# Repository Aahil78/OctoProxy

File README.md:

# OctoProxy

OctoProxy is a raspberry pi based OctoPrint server for the Bambu Lab A1, it acts as a proxy for region locked and LAN Only mode printers to have remote monitoring and access. It also has a Tailscale VPN server to trick Bambu Studio to think you are on  your LAN when you arent, this will allow you to send prints from Bambu Studio to any LAN Only printer from anywhere in the world. You can also use it as a printago fuse or simplyprint server.

Features:
  - Runs OctoPrint allowing you to send prints from anywhere.
  - Uses a Raspberry Pi 4 as the SBC, allowing for upgrades like sensors, lights, software upgrades, and more.
  - WS2812B/SK6812 3 Pin connector for custom lights.
  - Has a CSI Camera, allowing better timelapses and better video streaming footage. We all know the A1 Camera is..... special.
  - GPIO Pins broken out for upgrades.

## Images

### PCB:

### Case:

(Top has magnets embedded)

### Schematic:

## BOM:

| Item:                            | Quantity: | Price: | Link:                | Total Cost:                   |
|----------------------------------|-----------|--------|----------------------|-------------------------------|
| Raspberry Pi 4 (Already have it) | 1         | $0     | N/A                  |                               |
| Raspberry Pi 4 Camera            | 1         | $23.08 | Camera               |                               |
| PCB                              | 1         | $15.78 |                      |                               |
| Raspberry Pi Fan                 | 1         | $4.35  | Fan                  |                               |
| Standoffs & Screws               | 1 kit     | $10    | Screws and standoffs |                               |
| 3 Pin Female Header              | 3         | $2.50  | 3 Pin Header         |                               |
| 4 Pin Female Header              | 2         | $2.72  | 4 Pin Header         |                               |
| 7 Pin Female Header              | 1         | $3.10  | 7 Pin Header         |                               |
| 6 Pin Female Header              | 2         | $2.95  | 6 Pin Header         |                               |
| 2 Pin Male Header                | 1         | $1.00  | 2 Pin Header         |                               |
| 1 Pin Header                     | 1         | $1     | 1 Pin Header         |                               |
| 330ohm Resistor                  | 1         | $1.47  | Resistor             |                               |
| 40Pin SMT Connector              | 1         | $4.77  | SMT Connector        |                               |
| WS2812B LED Strip                | 1         | $6.46  | LED Strip            |                               |
|                                  |           |        |                      | 79.18 (Will pay extra myself) |

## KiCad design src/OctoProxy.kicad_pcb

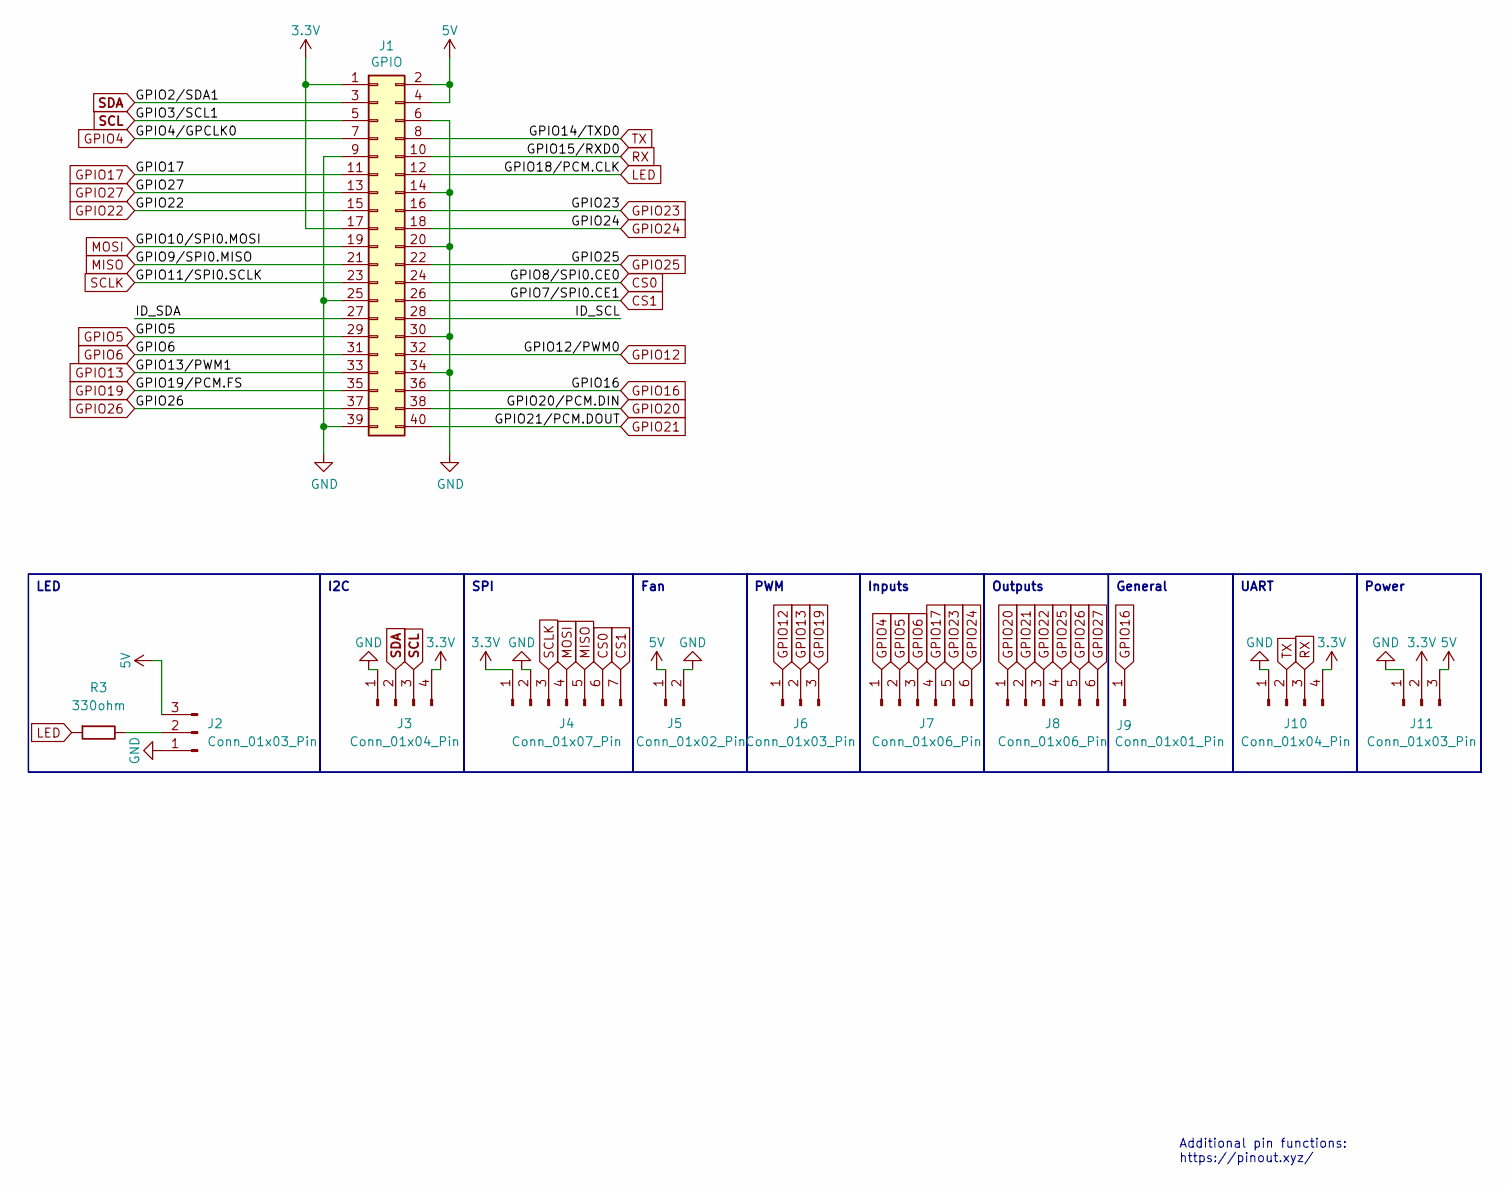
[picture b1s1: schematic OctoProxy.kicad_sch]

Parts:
J1: GPIO; Raspberry_Pi_Shield_Bottom_Entry_No_Mounting_Holes
J2, J6, J11: Conn_01x03_Pin; Harwin_M20-89003xx_1x03_P2.54mm_Horizontal
J3, J10: Conn_01x04_Pin; Harwin_M20-89004xx_1x04_P2.54mm_Horizontal
J4: Conn_01x07_Pin; Harwin_M20-89007xx_1x07_P2.54mm_Horizontal
J5: Conn_01x02_Pin; PinHeader_1x02_P2.54mm_Horizontal
J7, J8: Conn_01x06_Pin; Harwin_M20-89006xx_1x06_P2.54mm_Horizontal
J9: Conn_01x01_Pin; PinHeader_1x01_P2.54mm_Horizontal
R3: 330ohm; R_Axial_DIN0207_L6.3mm_D2.5mm_P10.16mm_Horizontal

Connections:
3.3V: J1.1, J1.17, J3.4, J4.1, J10.4, J11.2
5V: J1.2, J1.4, J2.3, J5.1, J11.3
/ID_SCL: J1.28
/ID_SDA: J1.27
CS0: J1.24, J4.6
CS1: J1.26, J4.7
GND: J1.6, J1.9, J1.14, J1.20, J1.25, J1.30, J1.34, J1.39, J2.1, J3.1, J4.2, J5.2, J10.1, J11.1
GPIO4: J1.7, J7.1
GPIO5: J1.29, J7.2
GPIO6: J1.31, J7.3
GPIO12: J1.32, J6.1
GPIO13: J1.33, J6.2
GPIO16: J1.36, J9.1
GPIO17: J1.11, J7.4
GPIO19: J1.35, J6.3
GPIO20: J1.38, J8.1
GPIO21: J1.40, J8.2
GPIO22: J1.15, J8.3
GPIO23: J1.16, J7.5
GPIO24: J1.18, J7.6
GPIO25: J1.22, J8.4
GPIO26: J1.37, J8.5
GPIO27: J1.13, J8.6
LED: J1.12, R3.1
MISO: J1.21, J4.5
MOSI: J1.19, J4.4
unnamed: J2.2, R3.2
RX: J1.10, J10.3
SCL: J1.5, J3.3
SCLK: J1.23, J4.3
SDA: J1.3, J3.2
TX: J1.8, J10.2

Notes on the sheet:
Additional pin functions: https://pinout.xyz/
Outputs
UART
LED
Power
I2C
SPI
PWM
Inputs
Fan
General

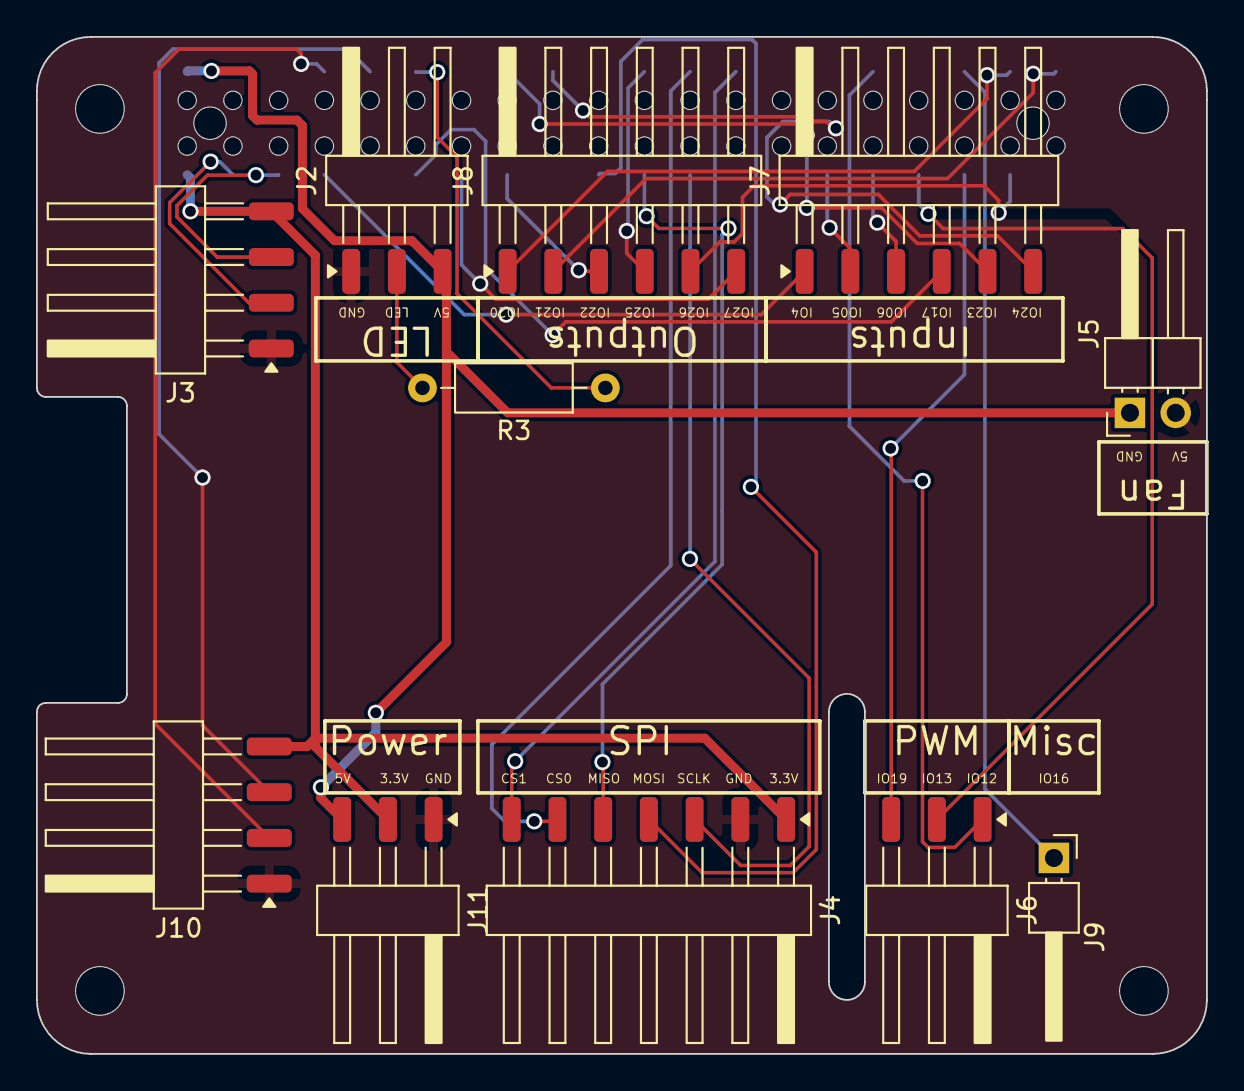
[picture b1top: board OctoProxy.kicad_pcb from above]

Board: 2 copper layers, 65.0 x 56.5 mm, 16 parts (0 on the bottom side), 30 nets.

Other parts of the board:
MH1, MH2, MH3, MH4: MountingHole_2.7mm_M2.5

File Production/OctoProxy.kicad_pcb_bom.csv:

Designator,Quantity,Value,Footprint,Package,MPN,DNP,Mount_Type,Description
J1,1,GPIO,Raspberry_Pi_Shield_Bottom_Entry_No_Mounting_Holes,,,,tht,
"J10, J3",2,Conn_01x04_Pin,Harwin_M20-89004xx_1x04_P2.54mm_Horizontal,,,,smt,
"J11, J2, J6",3,Conn_01x03_Pin,Harwin_M20-89003xx_1x03_P2.54mm_Horizontal,,,,smt,
J4,1,Conn_01x07_Pin,Harwin_M20-89007xx_1x07_P2.54mm_Horizontal,,,,smt,
J5,1,Conn_01x02_Pin,PinHeader_1x02_P2.54mm_Horizontal,,,,tht,"Generic connector, single row, 01x02, script generated"
"J7, J8",2,Conn_01x06_Pin,Harwin_M20-89006xx_1x06_P2.54mm_Horizontal,,,,smt,
J9,1,Conn_01x01_Pin,PinHeader_1x01_P2.54mm_Horizontal,,,,tht,"Generic connector, single row, 01x01, script generated"
R3,1,330ohm,R_Axial_DIN0207_L6.3mm_D2.5mm_P10.16mm_Horizontal,,,,tht,"330Ω, 1/4W Resistor"

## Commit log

2026-02-26 Add JOURNAL,md
    Documented brainstorming and schematic creation for OctoProxy.
2026-02-26 Add journal entry for PCB creation
    Documented the creation of the PCB and time spent.
2026-02-27 Document pin labeling on PCB
    Labeled all pins on the PCB and noted labeling limitations.
2026-02-27 Revise timestamps and add new journal entries
    Corrected timestamp formatting and added new journal entries detailing the labeling of pins and component population on the PCB.
2026-03-02 Update JOURNAL.md with March 3rd entry
    Added journal entry for March 3rd detailing progress on case bottom.
2026-03-02 Add files
2026-03-05 Fix BOM.csv formatting and update item details
